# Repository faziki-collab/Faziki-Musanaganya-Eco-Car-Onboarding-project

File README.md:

# Faziki-Musanaganya-Eco-Car-Onboarding-project

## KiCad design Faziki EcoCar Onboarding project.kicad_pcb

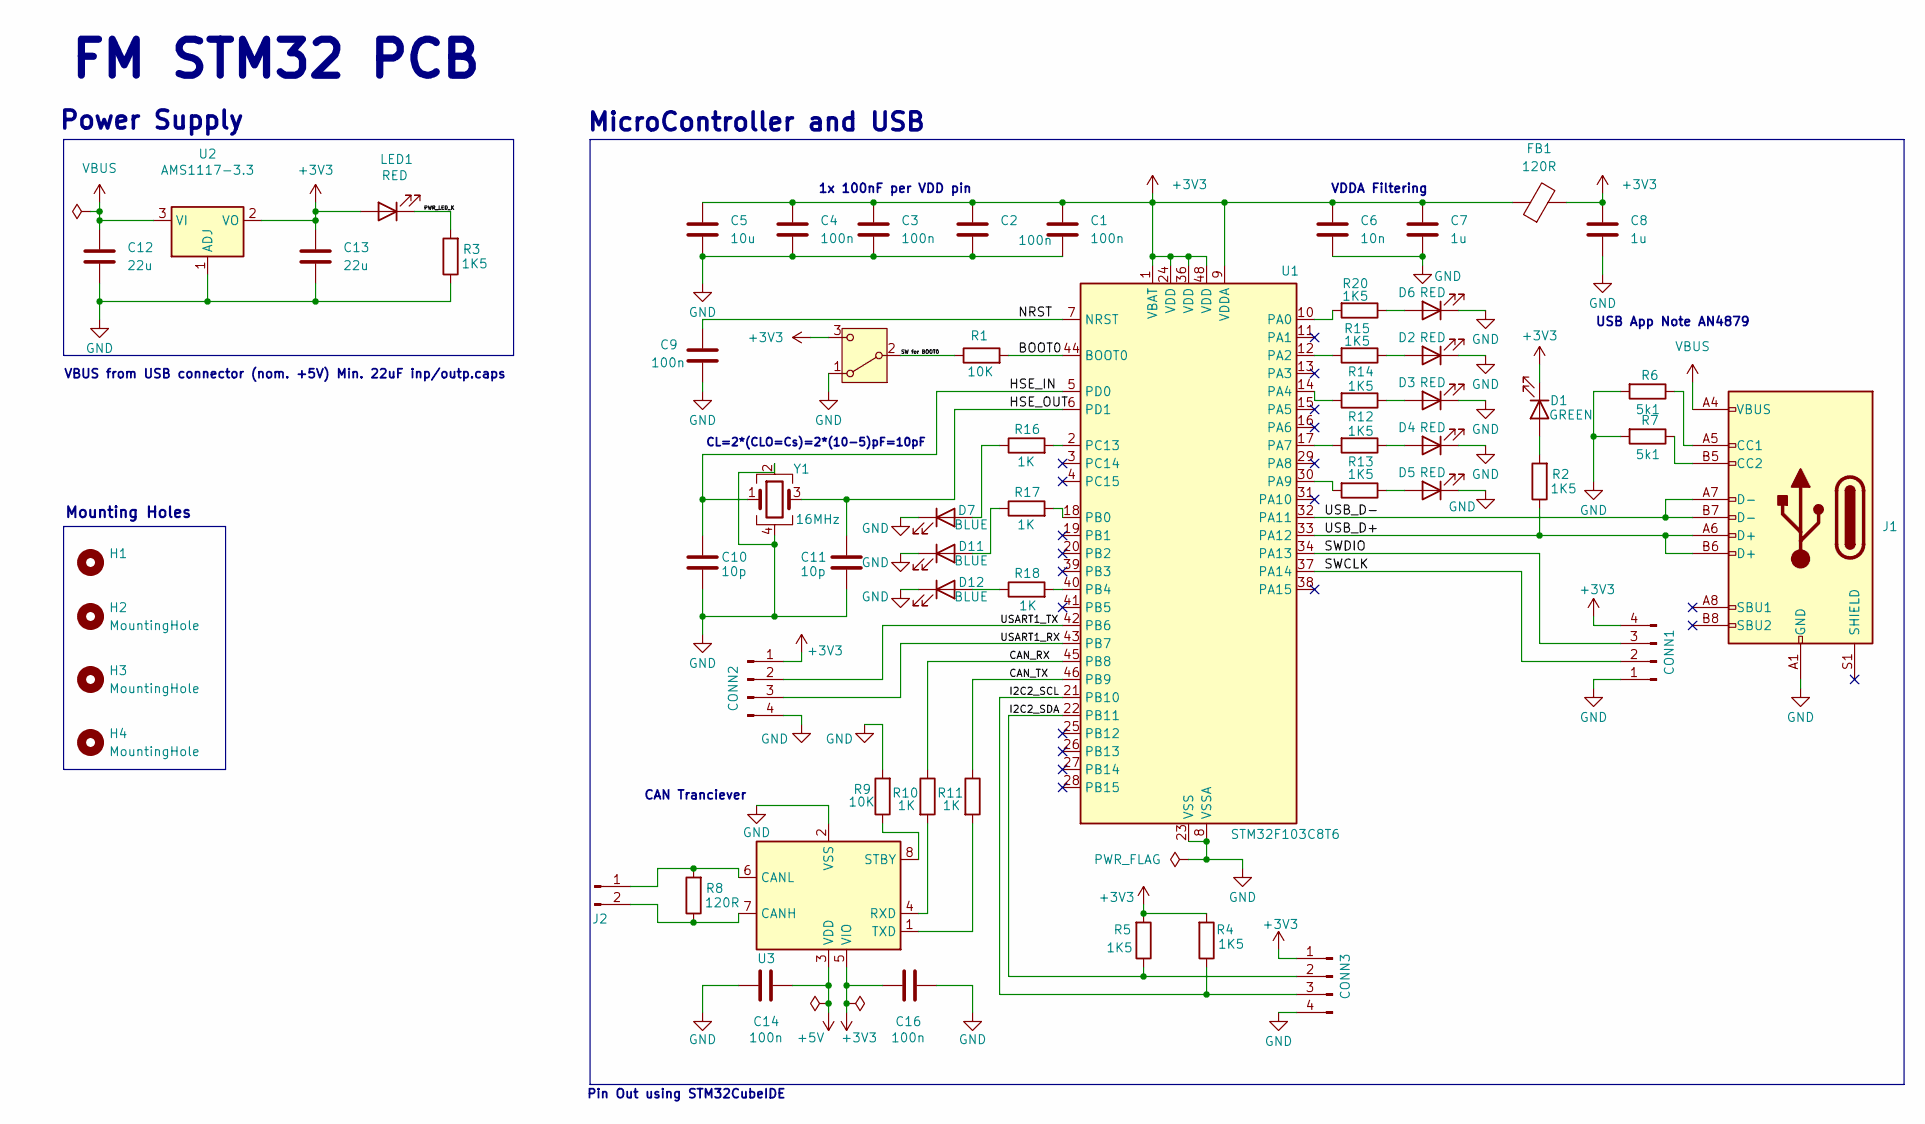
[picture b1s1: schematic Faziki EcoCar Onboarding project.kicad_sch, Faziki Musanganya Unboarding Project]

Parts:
C1, C2, C3, C9, C14, C16: 100n; C_0402_1005Metric
C4: 100n; C_0402_1005Metric_Pad0.74x0.62mm_HandSolder
C5: 10u; C_0603_1608Metric
C6: 10n; C_0402_1005Metric
C7, C8: 1u; C_0402_1005Metric
C10, C11: 10p; C_0402_1005Metric
C12, C13: 22u; C_0805_2012Metric
CONN1, CONN2, CONN3: Conn_01x04_Pin; PinHeader_1x04_P2.54mm_Vertical
D1: GREEN; LED_0603_1608Metric
D2, D3, D4, D5, D6: RED; LED_0603_1608Metric
D7, D11, D12: BLUE; LED_0603_1608Metric
FB1: 120R; L_0603_1608Metric
H1, H2, H3, H4: MountingHole; MountingHole_2.2mm_M2
J1: USB_C_Receptacle_USB2.0_16P; USB_C_Receptacle_GCT_USB4105-xx-A_16P_TopMnt_Horizontal
J2: Conn_01x02_Pin; PinHeader_1x02_P2.54mm_Vertical
LED1: RED; LED_0603_1608Metric
R1, R9: 10K; R_0402_1005Metric
R2, R3, R4, R5, R12, R13, R14, R15, R20: 1K5; R_0402_1005Metric
R6, R7: 5k1; R_0402_1005Metric
R8: 120R; R_0402_1005Metric
R10, R11, R16, R17, R18: 1K; R_0402_1005Metric
SW1: SW_SPDT; SW_SPDT_PCM12
U1: STM32F103C8T6; LQFP-48_7x7mm_P0.5mm
U2: AMS1117-3.3; SOT-223-3_TabPin2
U3: MCP2542FDxMF; DFN-8-1EP_3x3mm_P0.65mm_EP1.55x2.4mm
Y1: 16MHz; Crystal_SMD_3225-4Pin_3.2x2.5mm

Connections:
+3V3: C1.1, C2.1, C3.1, C4.1, C5.1, C6.1, C7.1, C8.1, C13.1, C16.1, CONN1.4, CONN2.1, CONN3.1, D1.1 (K), FB1.1, FB1.2, LED1.2 (A), R4.2, R5.2, SW1.3 (C), U1.1 (VBAT), U1.9 (VDDA), U1.24 (VDD), U1.36 (VDD), U1.48 (VDD), U2.2 (VO), U3.5 (VIO)
+5V: C14.2, U3.3 (VDD)
/BOOT0: R1.2, U1.44 (BOOT0)
/CAN_RX: R10.1, U1.45 (PB8)
/CAN_TX: R11.1, U1.46 (PB9)
/HSE_IN: C10.1, U1.5 (PD0), Y1.1
/HSE_OUT: C11.1, U1.6 (PD1), Y1.3
/I2C2_SCL: CONN3.3, R4.1, U1.21 (PB10)
/I2C2_SDA: CONN3.2, R5.1, U1.22 (PB11)
/NRST: C9.1, U1.7 (NRST)
/PWR_LED_K: LED1.1 (K), R3.2
/SW for BOOT0: R1.1, SW1.2 (B)
/SWCLK: CONN1.2, U1.37 (PA14)
/SWDIO: CONN1.3, U1.34 (PA13)
/USART1_RX: CONN2.3, U1.43 (PB7)
/USART1_TX: CONN2.2, U1.42 (PB6)
/USB_D+: J1.A6 (D+), J1.B6 (D+), R2.1, U1.33 (PA12); also elsewhere on the board
/USB_D-: J1.A7 (D-), J1.B7 (D-), U1.32 (PA11); also elsewhere on the board
GND: C1.2, C2.2, C3.2, C4.2, C5.2, C6.2, C7.2, C8.2, C9.2, C10.2, C11.2, C12.2, C13.2, C14.1, C16.2, CONN1.1, CONN2.4, CONN3.4, D2.1 (K), D3.1 (K), D4.1 (K), D5.1 (K), D6.1 (K), D7.1 (K), D11.1 (K), D12.1 (K), J1.A1 (GND), J1.A12 (GND), J1.B1 (GND), J1.B12 (GND), R3.1, R6.2, R7.2, R9.2, SW1.1 (A), U1.8 (VSSA), U1.23 (VSS), U1.35 (VSS), U1.47 (VSS), U2.1 (ADJ), U3.2 (VSS), U3.9 (VSS), Y1.2, Y1.4; also elsewhere on the board
unnamed: D1.2 (A), R2.2
unnamed: D2.2 (A), R15.1
unnamed: D3.2 (A), R14.1
unnamed: D4.2 (A), R12.1
unnamed: D5.2 (A), R13.1
unnamed: D6.2 (A), R20.1
unnamed: D7.2 (A), R16.1
unnamed: D11.2 (A), R17.1
unnamed: D12.2 (A), R18.1
unnamed 28: J1.A5 (CC1), R6.1; also elsewhere on the board
unnamed 29: J1.B5 (CC2), R7.1; also elsewhere on the board
unnamed: J2.1, R8.2, U3.6 (CANL)
unnamed: J2.2, R8.1, U3.7 (CANH)
unnamed: R20.2, U1.10 (PA0)
unnamed: R15.2, U1.12 (PA2)
unnamed: R14.2, U1.14 (PA4)
unnamed: R12.2, U1.17 (PA7)
unnamed: R13.2, U1.30 (PA9)
unnamed: R17.2, U1.18 (PB0)
unnamed: R18.2, U1.40 (PB4)
unnamed: R16.2, U1.2 (PC13)
unnamed: R10.2, U3.4 (RXD)
unnamed: R9.1, U3.8 (STBY)
unnamed: R11.2, U3.1 (TXD)
VBUS: C12.1, J1.A4 (VBUS), J1.A9 (VBUS), J1.B4 (VBUS), J1.B9 (VBUS), U2.3 (VI); also elsewhere on the board

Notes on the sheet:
USB App Note AN4879
MicroController and USB
CL=2*(CLO=Cs)=2*(10-5)pF=10pF
FM STM32 PCB
VBUS from USB connector (nom. +5V) Min. 22uF inp/outp.caps
VDDA Filtering
CAN Tranciever
Mounting Holes
Power Supply
Pin Out using STM32CubeIDE
1x 100nF per VDD pin

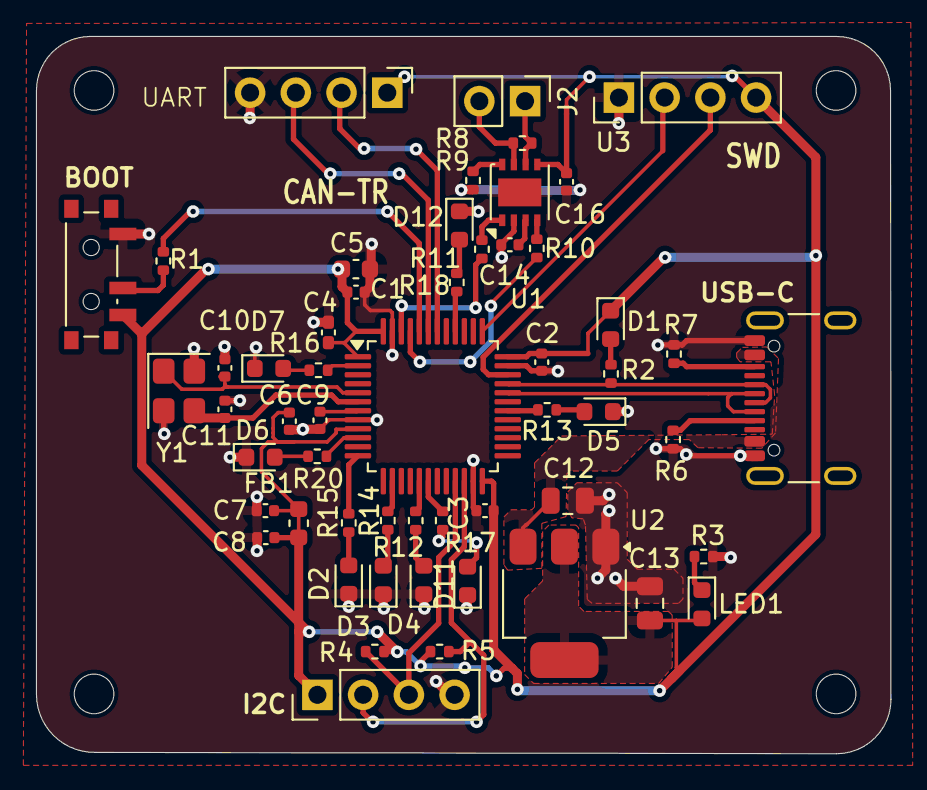
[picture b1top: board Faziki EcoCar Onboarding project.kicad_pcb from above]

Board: 2 copper layers, 47.5 x 39.8 mm, 59 parts (0 on the bottom side), 44 nets.

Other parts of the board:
USB-C: USB_C_Receptacle_USB2.0_16P; USB_C_Receptacle_GCT_USB4105-xx-A_16P_TopMnt_Horizontal

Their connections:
/USB_D+: USB-C.A6 (D+), USB-C.B6 (D+); also elsewhere on the board
/USB_D-: USB-C.A7 (D-), USB-C.B7 (D-); also elsewhere on the board
GND: USB-C.A1 (GND), USB-C.A12 (GND), USB-C.B1 (GND), USB-C.B12 (GND); also elsewhere on the board
unnamed 28: USB-C.A5 (CC1); also elsewhere on the board
unnamed 29: USB-C.B5 (CC2); also elsewhere on the board
VBUS: USB-C.A4 (VBUS), USB-C.A9 (VBUS), USB-C.B4 (VBUS), USB-C.B9 (VBUS); also elsewhere on the board
